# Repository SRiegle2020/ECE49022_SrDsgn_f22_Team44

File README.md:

# ECE49022_SrDsgn_f22_Team44
ECE49022, Team44, f2022. Biometric "Smart" Watch.
This project aims to display important vital signs to a user in a self-contained watch. The device will specifically track SpO2, heart rate, temperature,
steps walked, and calories consumed. More information to be added to this README.md later.

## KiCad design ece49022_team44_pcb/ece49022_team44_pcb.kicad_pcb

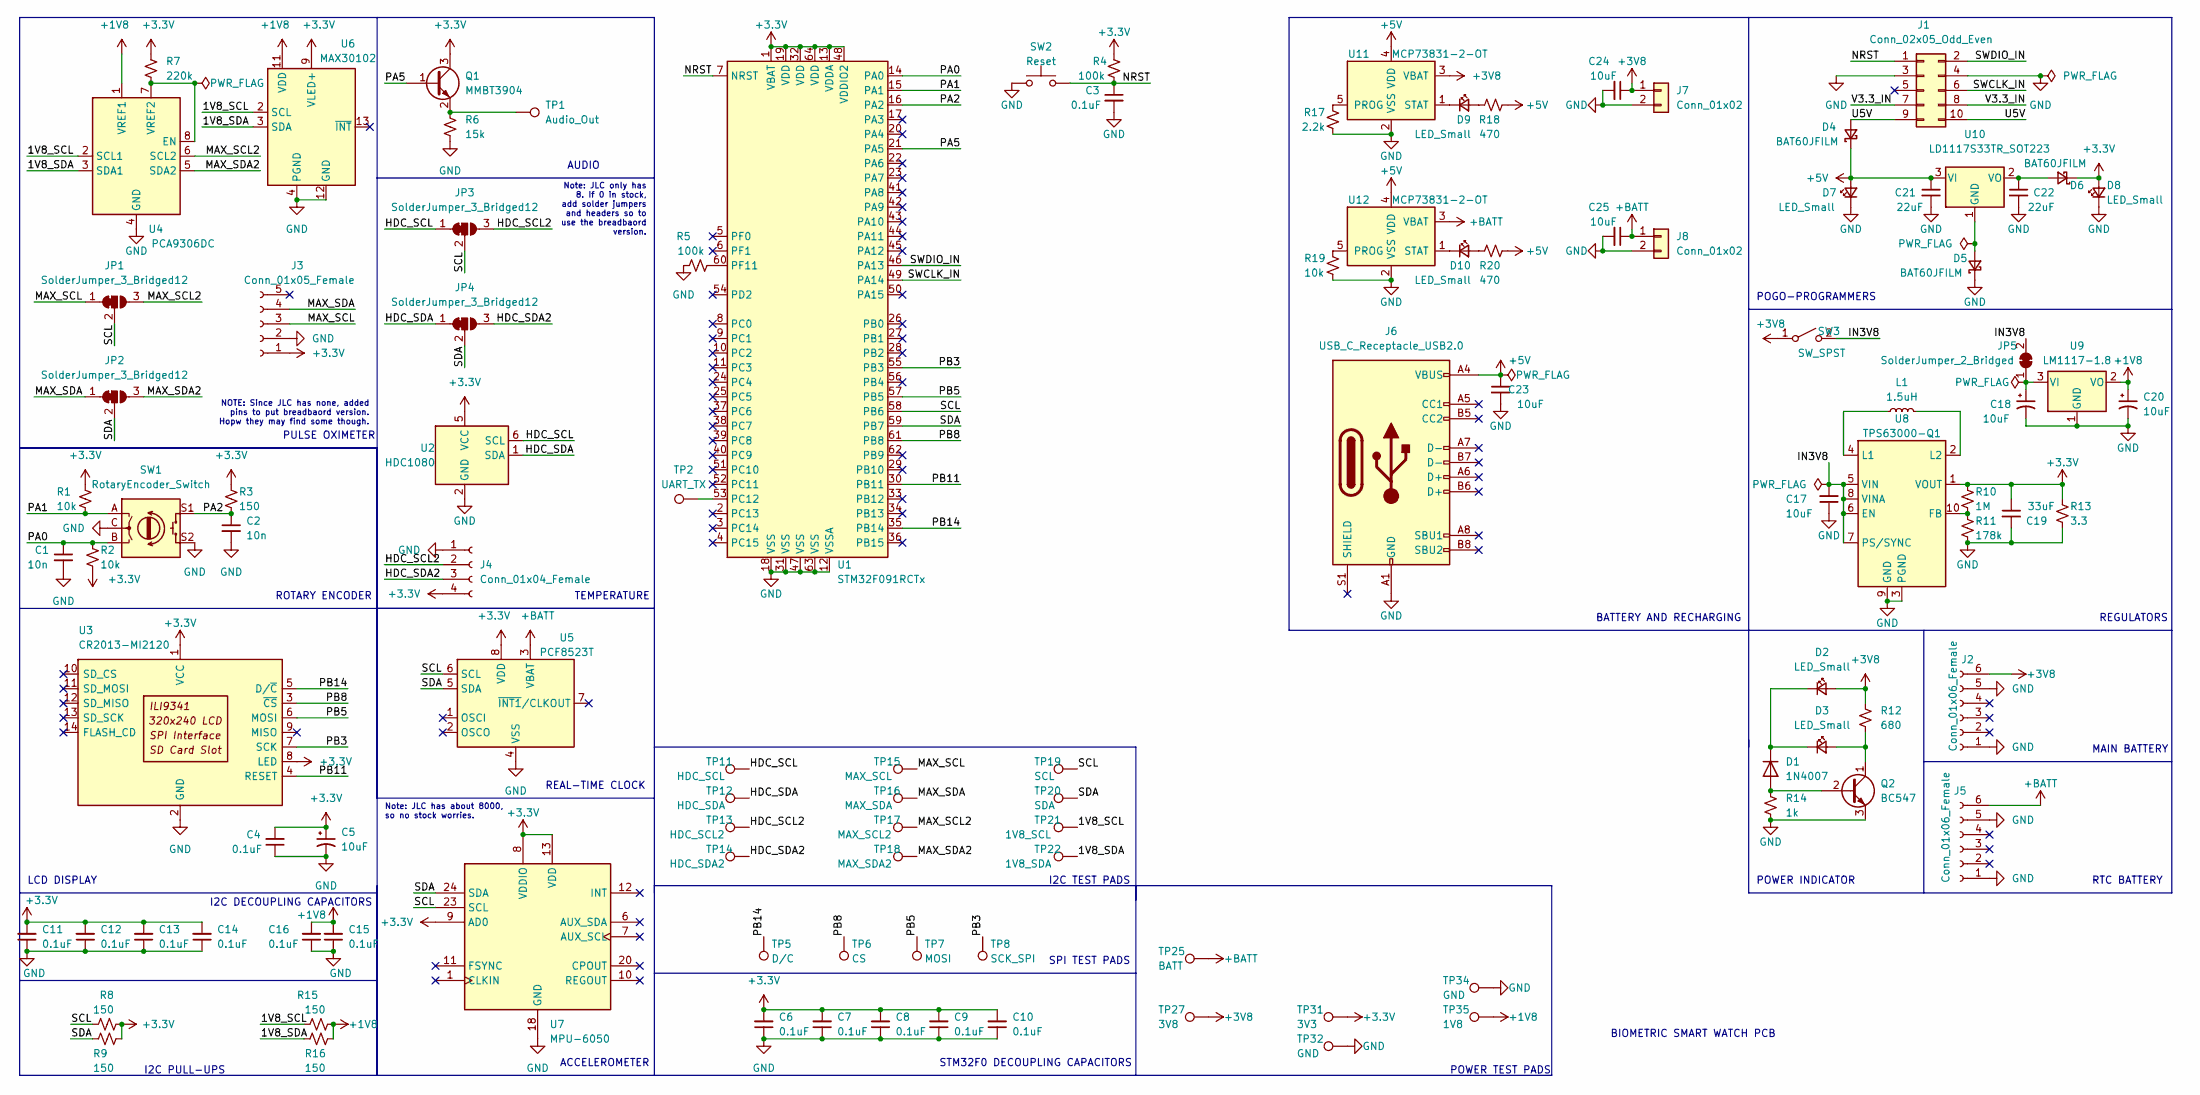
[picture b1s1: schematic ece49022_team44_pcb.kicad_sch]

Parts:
C1, C2: 10n; C_0201_0603Metric; LCSC C285010
C3, C4, C6, C7, C8, C9, C10, C11, C12, C13, C14, C15, C16: 0.1uF; C_0201_0603Metric; LCSC C284966
C5, C17, C18, C20, C23, C24, C25: 10uF; C_0402_1005Metric; LCSC C163694
C19: 33uF; CP_EIA-3528-21_Kemet-B; LCSC C723311
C21, C22: 22uF; C_0402_1005Metric; LCSC C415703
D1: 1N4007; D_SMA; LCSC C727081
D2: LED_Small; LED_0603_1608Metric; LCSC C72043
D3: LED_Small; LED_0603_1608Metric; LCSC C2286
D4, D5, D6: BAT60JFILM; D_SOD-323; LCSC C133103
D7, D8, D9, D10: LED_Small; LED_0603_1608Metric; LCSC C72038
J1: Conn_02x05_Odd_Even; Tag-Connect_TC2050-IDC-NL_2x05_P1.27mm_Vertical
J2, J5: Conn_01x06_Female; PinSocket_1x06_P2.54mm_Vertical
J3: Conn_01x05_Female; PinSocket_1x05_P2.54mm_Vertical
J4: Conn_01x04_Female; PinHeader_1x04_P2.54mm_Vertical
J6: USB_C_Receptacle_USB2.0; USB_C_Receptacle_XKB_U262-16XN-4BVC11; LCSC C2927038
J7, J8: Conn_01x02; JST_PH_S2B-PH-K_1x02_P2.00mm_Horizontal; LCSC C265016
JP1, JP2, JP3, JP4: SolderJumper_3_Bridged12; SolderJumper-3_P1.3mm_Bridged12_Pad1.0x1.5mm
JP5: SolderJumper_2_Bridged; SolderJumper-2_P1.3mm_Bridged2Bar_Pad1.0x1.5mm
L1: 1.5uH; L_0805_2012Metric; LCSC C281090
Q1: MMBT3904; SOT-23; LCSC C8512
Q2: BC547; TO-92_Inline; LCSC C713613
R1, R2, R19: 10k; R_0201_0603Metric; LCSC C473048
R3, R8, R9, R15, R16: 150; R_0201_0603Metric; LCSC C246814
R4, R5: 100k; R_0201_0603Metric; LCSC C270364
R6: 15k; R_0201_0603Metric; LCSC C473455
R7: 220k; R_0603_1608Metric; LCSC C22961
R10: 1M; R_0402_1005Metric; LCSC C26083
R11: 178k; R_0402_1005Metric; LCSC C185459
R12: 680; R_0201_0603Metric; LCSC C473509
R13: 3.3; R_0603_1608Metric; LCSC C22979
R14: 1k; R_0201_0603Metric; LCSC C102683
R17: 2.2k; R_0201_0603Metric; LCSC C142018
R18, R20: 470; R_0201_0603Metric; LCSC C473464
SW1: RotaryEncoder_Switch; RotaryEncoder_Alps_EC11E-Switch_Vertical_H20mm_CircularMoun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; LCSC C370986
SW2: Reset; SW_SPST_Omron_B3FS-101xP; LCSC C271753
SW3: SW_SPST; SW_DIP_SPSTx01_Slide_Copal_CHS-01B_W7.62mm_P1.27mm; LCSC C3293141
TP1: Audio_Out; TestPoint_Pad_D2.5mm
TP2: UART_TX; TestPoint_Pad_D2.5mm
TP5: D/C; TestPoint_Pad_D2.5mm
TP6: CS; TestPoint_Pad_D2.5mm
TP7: MOSI; TestPoint_Pad_D2.5mm
TP8: SCK_SPI; TestPoint_Pad_D2.5mm
TP11: HDC_SCL; TestPoint_Pad_D2.5mm
TP12: HDC_SDA; TestPoint_Pad_D2.5mm
TP13: HDC_SCL2; TestPoint_Pad_D2.5mm
TP14: HDC_SDA2; TestPoint_Pad_D2.5mm
TP15: MAX_SCL; TestPoint_Pad_D2.5mm
TP16: MAX_SDA; TestPoint_Pad_D2.5mm
TP17: MAX_SCL2; TestPoint_Pad_D2.5mm
TP18: MAX_SDA2; TestPoint_Pad_D2.5mm
TP19: SCL; TestPoint_Pad_D2.5mm
TP20: SDA; TestPoint_Pad_D2.5mm
TP21: 1V8_SCL; TestPoint_Pad_D2.5mm
TP22: 1V8_SDA; TestPoint_Pad_D2.5mm
TP25: BATT; TestPoint_Pad_D2.5mm
TP27: 3V8; TestPoint_Pad_D2.5mm
TP31: 3V3; TestPoint_Pad_D2.5mm
TP32, TP34: GND; TestPoint_Pad_D2.5mm
TP35: 1V8; TestPoint_Pad_D2.5mm
U1: STM32F091RCTx; LQFP-64_10x10mm_P0.5mm; LCSC C89056
U2: HDC1080; Texas_PWSON-N6; LCSC C82227
U3: CR2013-MI2120
U4: PCA9306DC; VSSOP-8_2.3x2mm_P0.5mm; LCSC C33196
U5: PCF8523T; SOIC-8_3.9x4.9mm_P1.27mm; LCSC C2651516
U6: MAX30102; Maxim_OLGA-14_3.3x5.6mm_P0.8mm; LCSC C9900007468
U7: MPU-6050; InvenSense_QFN-24_4x4mm_P0.5mm; LCSC C24112
U8: TPS63000-Q1; Texas_DRC0010J_ThermalVias; LCSC C523783
U9: LM1117-1.8; TO-252-2; LCSC C38160
U10: LD1117S33TR_SOT223; SOT-223-3_TabPin2; LCSC C35879
U11, U12: MCP73831-2-OT; SOT-23-5; LCSC C424093

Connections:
+1V8: C15.2, C16.2, C20.1, R15.1, R16.2, TP35.1, U4.1 (VREF1), U6.11 (VDD), U9.2 (VO)
+3V3: C4.2, C5.1, C6.2, C7.2, C8.2, C9.2, C10.2, C11.2, C12.2, C13.2, C14.2, C19.1, D6.1 (K), D8.2 (A), J3.1, J4.4, Q1.3 (C), R1.2, R2.1, R3.2, R4.1, R7.1, R8.1, R9.2, R10.1, R13.1, TP31.1, U1.1 (VBAT), U1.13 (VDDA), U1.19 (VDD), U1.32 (VDD), U1.48 (VDDIO2), U1.64 (VDD), U2.5 (VCC), U3.1 (VCC), U3.8 (LED), U5.8 (VDD), U6.9 (VLED+), U6.10 (VLED+), U7.8 (VDDIO), U7.9 (AD0), U7.13 (VDD), U8.1 (VOUT)
+3V8: C24.1, D2.2 (A), J2.6, J7.1, R12.1, SW3.1 (A), TP27.1, U11.3 (VBAT)
+5V: C21.1, C23.1, D4.1 (K), D7.2 (A), J6.A4 (VBUS), J6.A9 (VBUS), J6.B4 (VBUS), J6.B9 (VBUS), R18.2, R20.1, U10.3 (VI), U11.4 (VDD), U12.4 (VDD)
+BATT: C25.1, J5.6, J8.1, TP25.1, U5.3 (VBAT), U12.3 (VBAT)
/1V8_SCL: R15.2, TP21.1, U4.2 (SCL1), U6.2 (SCL)
/1V8_SDA: R16.1, TP22.1, U4.3 (SDA1), U6.3 (SDA)
/HDC_SCL: JP3.1 (A), TP11.1, U2.6 (SCL)
/HDC_SCL2: J4.2, JP3.3 (B), TP13.1
/HDC_SDA: JP4.1 (A), TP12.1, U2.1 (SDA)
/HDC_SDA2: J4.3, JP4.3 (B), TP14.1
/IN3V8: C17.2, JP5.2 (B), SW3.2 (B), U8.5 (VIN), U8.6 (EN), U8.7 (PS/SYNC), U8.8 (VINA)
/MAX_SCL: J3.3, JP1.1 (A), TP15.1
/MAX_SCL2: JP1.3 (B), TP17.1, U4.6 (SCL2)
/MAX_SDA: J3.4, JP2.1 (A), TP16.1
/MAX_SDA2: JP2.3 (B), TP18.1, U4.5 (SDA2)
/NRST: C3.1, J1.1, R4.2, SW2.2, U1.7 (NRST)
/PA0: C1.1, R2.2, SW1.B, U1.14 (PA0)
/PA1: R1.1, SW1.A, U1.15 (PA1)
/PA2: C2.1, R3.1, SW1.S1, U1.16 (PA2)
/PA5: Q1.1 (B), U1.21 (PA5)
/PB3: TP8.1, U1.55 (PB3), U3.7 (SCK)
/PB5: TP7.1, U1.57 (PB5), U3.6 (MOSI)
/PB8: TP6.1, U1.61 (PB8), U3.3 (~CS)
/PB11: U1.30 (PB11), U3.4 (RESET)
/PB14: TP5.1, U1.35 (PB14), U3.5 (D/~C)
/SCL: JP1.2 (C), JP3.2 (C), R8.2, TP19.1, U1.58 (PB6), U5.6 (SCL), U7.23 (SCL)
/SDA: JP2.2 (C), JP4.2 (C), R9.1, TP20.1, U1.59 (PB7), U5.5 (SDA), U7.24 (SDA)
/SWCLK_IN: J1.6, U1.49 (PA14)
/SWDIO_IN: J1.2, U1.46 (PA13)
/U5V: D4.2 (A), J1.9, J1.10
/V3.3_IN: J1.7, J1.8
GND: C1.2, C2.2, C3.2, C4.1, C5.2, C6.1, C7.1, C8.1, C9.1, C10.1, C11.1, C12.1, C13.1, C14.1, C15.1, C16.1, C17.1, C18.2, C19.2, C20.2, C21.2, C22.2, C23.2, C24.2, C25.2, D5.1 (K), D7.1 (K), D8.1 (K), J1.3, J1.4, J2.1, J2.5, J3.2, J4.1, J5.1, J5.5, J6.A1 (GND), J6.A12 (GND), J6.B1 (GND), J6.B12 (GND), J7.2, J8.2, Q2.3 (E), R5.2, R6.2, R11.2, R13.2, R14.2, R17.1, R19.1, SW1.C, SW1.S2, SW2.1, TP32.1, TP34.1, U1.12 (VSSA), U1.18 (VSS), U1.31 (VSS), U1.47 (VSS), U1.63 (VSS), U2.2 (GND), U3.2 (GND), U4.4 (GND), U5.4 (VSS), U6.4 (PGND), U6.12 (GND), U7.18 (GND), U8.3 (PGND), U8.9 (GND), U8.11 (PGND), U9.1 (GND), U11.2 (VSS), U12.2 (VSS)
unnamed: C18.1, JP5.1 (A), U9.3 (VI)
unnamed: C22.1, D6.2 (A), U10.2 (VO)
unnamed: D1.1 (A), Q2.2 (B), R14.1
unnamed: D1.2 (K), D2.1 (K), D3.1 (K)
unnamed: D3.2 (A), Q2.1 (C), R12.2
unnamed: D5.2 (A), U10.1 (GND)
unnamed: D9.1 (K), U11.1 (STAT)
unnamed: D9.2 (A), R18.1
unnamed: D10.1 (K), U12.1 (STAT)
unnamed: D10.2 (A), R20.2
unnamed: L1.1, U8.4 (L1)
unnamed: L1.2, U8.2 (L2)
unnamed: Q1.2 (E), R6.1, TP1.1
unnamed: R5.1, U1.60 (PF11)
unnamed: R7.2, U4.7 (VREF2), U4.8 (EN)
unnamed: R10.2, R11.1, U8.10 (FB)
unnamed: R17.2, U11.5 (PROG)
unnamed: R19.2, U12.5 (PROG)
unnamed: TP2.1, U1.53 (PC12)

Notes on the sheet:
POGO-PROGRAMMERS
BATTERY AND RECHARGING
Note: JLC only has 8. If 0 in stock, add solder jumpers and headers so to use the breadbaord version.
TEMPERATURE
REAL-TIME CLOCK
NOTE: Since JLC has none, added pins to put breadbaord version. Hopw they may find some though.
SPI TEST PADS
MAIN BATTERY
RTC BATTERY
I2C PULL-UPS
REGULATORS
ROTARY ENCODER
BIOMETRIC SMART WATCH PCB
I2C TEST PADS
Note: JLC has about 8000, so no stock worries.
POWER INDICATOR
PULSE OXIMETER
LCD DISPLAY
I2C DECOUPLING CAPACITORS
ACCELEROMETER
STM32F0 DECOUPLING CAPACITORS
AUDIO
POWER TEST PADS

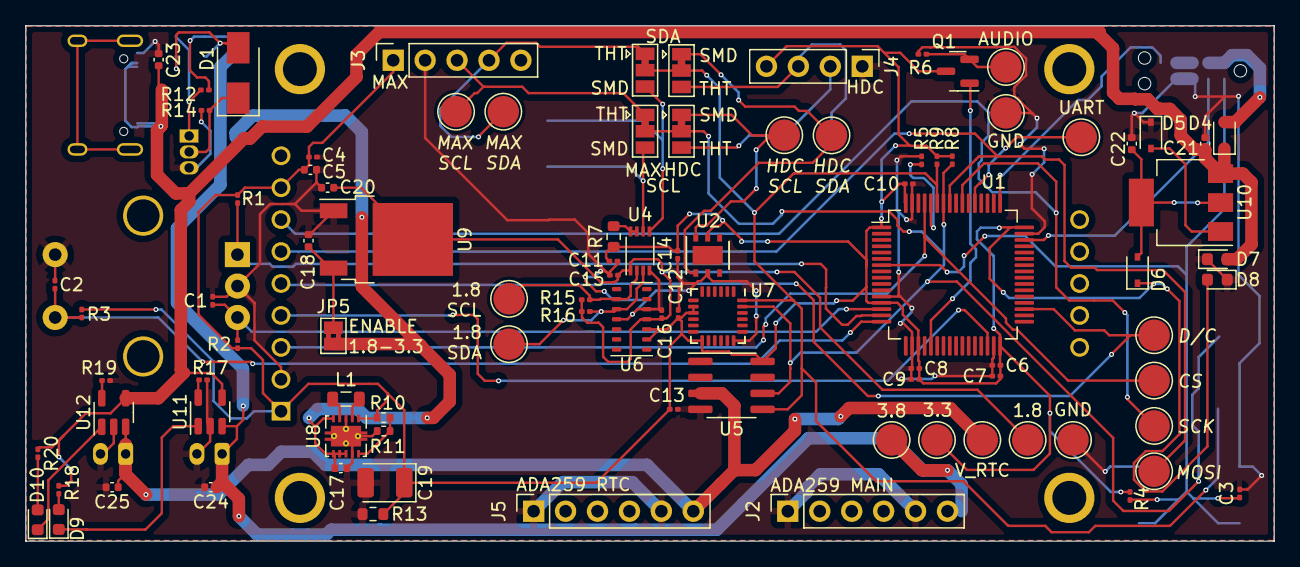
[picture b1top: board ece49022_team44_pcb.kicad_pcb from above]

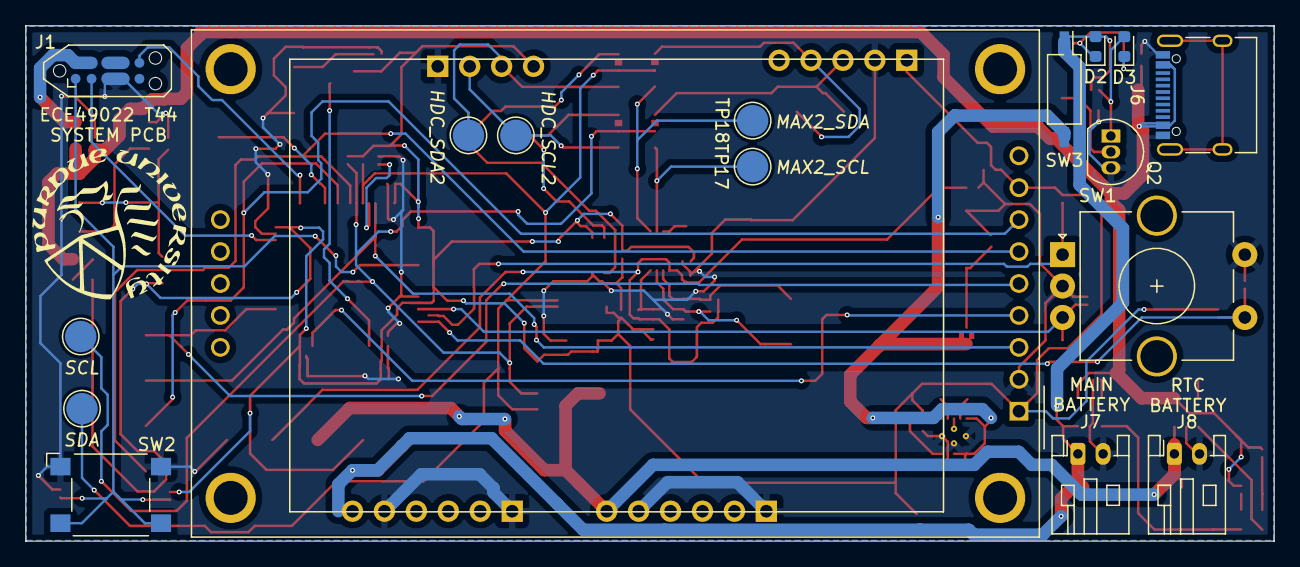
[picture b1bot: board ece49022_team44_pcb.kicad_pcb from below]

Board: 2 copper layers, 99.3 x 41.0 mm, 110 parts (17 on the bottom side), 52 nets.

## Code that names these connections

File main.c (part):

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
void init_exti(void) {
    RCC->AHBENR  |=  RCC_AHBENR_GPIOAEN;            //Clock GPIOA
    GPIOA->MODER &= ~(GPIO_MODER_MODER0             //Configure PA0-2 as inputs
                    | GPIO_MODER_MODER1
                    | GPIO_MODER_MODER2);
    GPIOA->MODER |= GPIO_MODER_MODER5_0;            //Set PA5 to output
    GPIOA->PUPDR &= ~(GPIO_PUPDR_PUPDR0             //Set PUPDR
                    | GPIO_PUPDR_PUPDR1);
    GPIOA->PUPDR |=  (GPIO_PUPDR_PUPDR0_0
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
    RCC->APB2ENR      |=  RCC_APB2ENR_SYSCFGCOMPEN;         //Clock the interrupt
    SYSCFG->EXTICR[1] &= ~(SYSCFG_EXTICR1_EXTI0_PA
                         | SYSCFG_EXTICR1_EXTI2_PA);        //Set to PA0, PA2
    EXTI->IMR         |=  EXTI_IMR_MR0 | EXTI_IMR_MR2;      //Unmask the interrupts for PA0,PA2
    EXTI->RTSR        |=  EXTI_RTSR_TR0;                    //Set to both rising and falling edge for PA0
    EXTI->FTSR        |=  EXTI_FTSR_TR0;
    EXTI->RTSR        |=  EXTI_RTSR_TR2;                    //Set to rising edge for PA2 (changes when button is RELEASED)

    NVIC->ISER[0] = 1 << EXTI0_1_IRQn;
    NVIC->ISER[0] = 1 << EXTI2_3_IRQn;  //Enable the interrupts
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
//==============================================================================
// EXTI2_3_IRQHandler
//  * Uses an EXTI for PA2 to detect if the encoder button was pressed.
//  * Cycles through the different configuration settings before returning to
//    display.
//==============================================================================
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
//==============================================================================
// EXTI0_1_IRQHandler
//  * Uses an EXTI for PA0 and PA1 to detect whether encoder is rotated.
//  * Changes settings based off of different modes.
//==============================================================================
void EXTI0_1_IRQHandler(void) {
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void init_spi1_slow() {
    RCC->APB2ENR  |=  RCC_APB2ENR_SPI1EN; //ENABLE SPI1 RCC CLOCK
    RCC->AHBENR   |=  RCC_AHBENR_GPIOBEN; //ENABLE GPIOB
    GPIOB->MODER  &= ~0XFC0;              //CLEAR PB3,4,5
    GPIOB->MODER  |=  0XA80;              //SET PB3,4,5 TO ALTFN
    GPIOB->AFR[0] &= ~0XFFF000;           //SET AFR3,4,5 TO AF0

    SPI1->CR1 &= ~SPI_CR1_SPE; //DISABLE SPI
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
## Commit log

2022-09-12 UART Libraries
    This is just a UART library to allow us to view variables on the serial port. It will only be used for debugging and will not be a part of the final project.
2022-09-14 BROKEN MAIN!
    Adding this so that I can MELD with old I2C functions, maybe find error in code.
2022-09-16 I2C and Sensors Libraries
    Added working libraries to use I2C and sensors. Sensor for accelerometer already added.
2022-09-17 All Accelerometer Stuff Working
    I got all the stuff for the accelerometer working, including accelerometer_X(), accerelometer_Y(), and accelerometer_Z() functions that return acceleration in each of those directions. The problems i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
2022-09-18 RTC Commands, Fixed I2C
    Added most RTC commands (except one for generating an interrupt; will be added in the future). Also added I2C functionality for both forms of I2C reading (with vs without a stop).
2022-09-18 Updated sensors.h
    Includes new sensors.h
2022-09-18 Updated sensors.c for New I2C Fixes
    Since I2C had to be fixed to use two different I2C protocols for reading (one with and one without a STOP), had to do some minor fixes to the sensors.c file.
2022-09-18 Updated to Account for New I2C
    Adjusted to work with updated I2C algorithms
2022-09-19 Rough Algorithms
    Incorporated rough algorithms for BMR, steps, and EE. Steps assumes a 100Hz sampling rate and returns a 1 if a rising edge (step) is detected and 0 otherwise. EE will manually track the energy expend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
    TO-DO:
    * Add functionality for allowing easy user interfacing
    * Figure out the weird floating-point bug
    * Review (including test) EE algorithm. Specifications say that we use Acc to get MET. However, algorithm doesn't incorporate this. Need to update?
    * Found an article that also used HR and EE. Perhaps combine the two (use a weighted average of both algorithms)?
2022-09-19 Some debugging
    Tried to fix the Energy Expenditure algorithm. Noticed that I was subtracting 1.3 everytime I sampled and not once. Should be fixed.
    Tested with a light jog and found readings to be about 10times higher than expected. Will do research to try and minimize error. May need new (or homemade) model.
2022-09-20 Finished Watch/Accelerometer Data Subsystem (v1)
    Finished the "bulk" of the watch and accelerometer data subsystem functions. Mostly just tidying-up code, increasing efficiency, and making it easier to transfer data to main.c for User-MCU subsystem.
    INDIVIDUAL TO-DO:
    * Add functions that return values*100 so they can be displayed on the screen
    * Add a RTC Watchdog that generates an interrupt every minute. This will be used to update time and for calculating EE.
    * Add a function that resets EE and Step counts at midnight.
    * Optimizations (currently using 11.2% of RAM to hold accelerometer data in an array. How to optimize?
2022-09-24 Minor Changes
    Added some minor changes, mainly a midnight function that resets EE counter at midnight.
2022-09-29 Updated EE Code
    Added functions to allow tracking DAILY vs EXERCISE EE.
    Modified the EE_IEEE function so that it returns the EE multiplied by 100 and casted as an integer (so we can return the data to main and retain two significant digits of data).
    TO-DO:
    * Add similar functionality to return the EE_exercise value to main (will take 30-40 seconds).
    * Continue to try and figure out how to use RTC interrupts.
    * Once a wearable PCB comes in, create a better model for calculating energy expenditure (maybe make a model based off of the Apple Watch instead of literature METs to obtain better accuracy for spec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
2022-10-04 Working PulseOx
    Pulse Ox is now semi-functional, with data being received from the MAX30102 and stored to a led_array global to the sensors.c file (5 seconds of 30Hz sampled data for Red and Infrared in the form [r0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
    TO-DO:
    * Algorithms to process the pulse-ox data to get SpO2 and HR.
2022-10-05 Work completely finished SpO2
    Stored the red and infrared sampled data into the array and determined min and max values for R value. Calibrated the data using excel to get the SpO2 value.
2022-10-05 EXTI for Rotary Encoder
    * Wrote external interrupts for rotary encoder and switch.
    * Code all in main. No updates to other functions.
2022-10-05 PCB Files
    Added the starting PCB files for the system PCB. Currently only includes rotary encoder. Will add in the future.
2022-10-06 Delete diskio.c
    Not using the SD card. Deleting diskio.c so no more "missing ff.c" errors when downloading new commits.
2022-10-06 Delete diskio.h
    Not using SD card, not needed, removes "unused .h file" warning.
2022-10-06 Cleaner Sensors, Added UART Test Debugging
    Cleaned all the code from Jason's commit (working Pulse Ox). Added a UART variable near the top of main.c. Changing this will turn on or off the UART to allow easier debugging in the future.
2022-10-06 Working Heart Rate
    Finished the Heart Rate algorithm. All sensors are working at the same time. All that is left is the temperature sensor and the user interface. PCB design will also be worked on throughout next week.
2022-10-06 Added Rotary Encoder Test Case
    Added a rotary encoder test case for midterm demo. Will also be used later.
2022-10-06 Working Display, Doesn't Update
    Creates an initial screen with values for different data. Works with all sensors.
    TO-DO:
    * Compartmentalize the stuff into functions.
    * Add update_display to timer to have screen update ONLY if a value has changed.
    * Add rotary encoder functionality.
2022-10-06 Working Display!
    Display works and updates once every five seconds. Due to some weird thingy, we get an error unless we reset the LCD each time (likely the sensors take too much time and cause the LCD to have issues)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
    TO-DO:
    * Rotary Encoder (Likely will disable everything, adjust stuff, then re-enable everything).
2022-10-07 Mostly Finished
    All sensors working, display working, encoder allows settings to change. Also resets EE and steps at midnight.
2022-10-08 Vital Checker Half-Working
    Can detect vital signs bad, but cannot get audio to work from the LC555 (wants higher power).
2022-10-08 Audio Working
    Added code to generate very choppy, annoying audio if a person starts dying. While not as nice sounding as a clean square wave, it does work at alerting the user they are dying.
    TO-DO:
    * Flash memory
    * PCB
2022-10-12 SCHEMATIC
    Initial schematics
    TO DO:
    * Test-pads
    * Solder jumpers for backup pins
2022-10-13 PCB Manufacturing
    Added the GERBERS, BOM, and POS files for PCB.
    Costs $270 to do one side, $360 to do both. Considering both so it works better, pay out of pocket.
2022-10-13 All PCB Stuff
    Uploaded changes to PCB (fixed the switch and LEDs). Also GERBERs and CENTROIDS, BOM. Checked on JLCPCB, $220 for build and assembly if only 2 boards.
    TO-DO:
    Double check silk-screen. Make sure comments look fine.
    Order PCB when fully reviewed.
2022-10-21 3D File
    3D File for making the 3D printed case
2022-10-26 Semi-Preservative Memory, 32Font, EE
    Able to save memory across software system resets, 32 bit font (kinda, to be fixed later), improved EE algorithm.
    TO-DO:
    * Prettitize the code (especially in main.c)
    * Better display
    * Case and mechanical engineering
    * Design Document 3
2022-10-27 32 and 48pt Font
    Configured LCD.C to use 32 and 48pt fonts.
    TO-DO:
    * Create custom font maps, convert to binary, add to table.
2022-10-27 Fixed 48pt Font
    Small error in 48pt font (only printed 3/4 of a character due to using a uint16t instead of uint32t).
2022-10-28 Testing Python Script
    Custom Font for 0, testing Python script before fixing everything
2022-11-02 Cleanup
2022-11-02 New Folder
2022-11-02 Remove
2022-11-02 Custom 32bit Font
    Translated images to custom 32bit font
2022-11-02 Custom 16bit Font
2022-11-02 16 and 32bit Fonts, Fixed Initial User Data
    Added custom 16bit and 32bit fonts. Also added code that ensures that if reprogramming the chip, user data is not impossible values.
    TO-DO:
    *48bit font
    *Finalize user interface and settings
2022-11-15 Adjusted accelerometer code to better detect steps
    NOTE: May need to redo the calorie consumption algorithm, may not.
2022-11-16 Updated main with border and new display
2022-11-16 New text display and border
2022-11-20 48Bit Font
    Added 48 bit font.
2022-12-15 FINAL PRODUCT
    Submission of the final product from SPARK challenge.
2022-12-15 Also the rev2 gerbers
